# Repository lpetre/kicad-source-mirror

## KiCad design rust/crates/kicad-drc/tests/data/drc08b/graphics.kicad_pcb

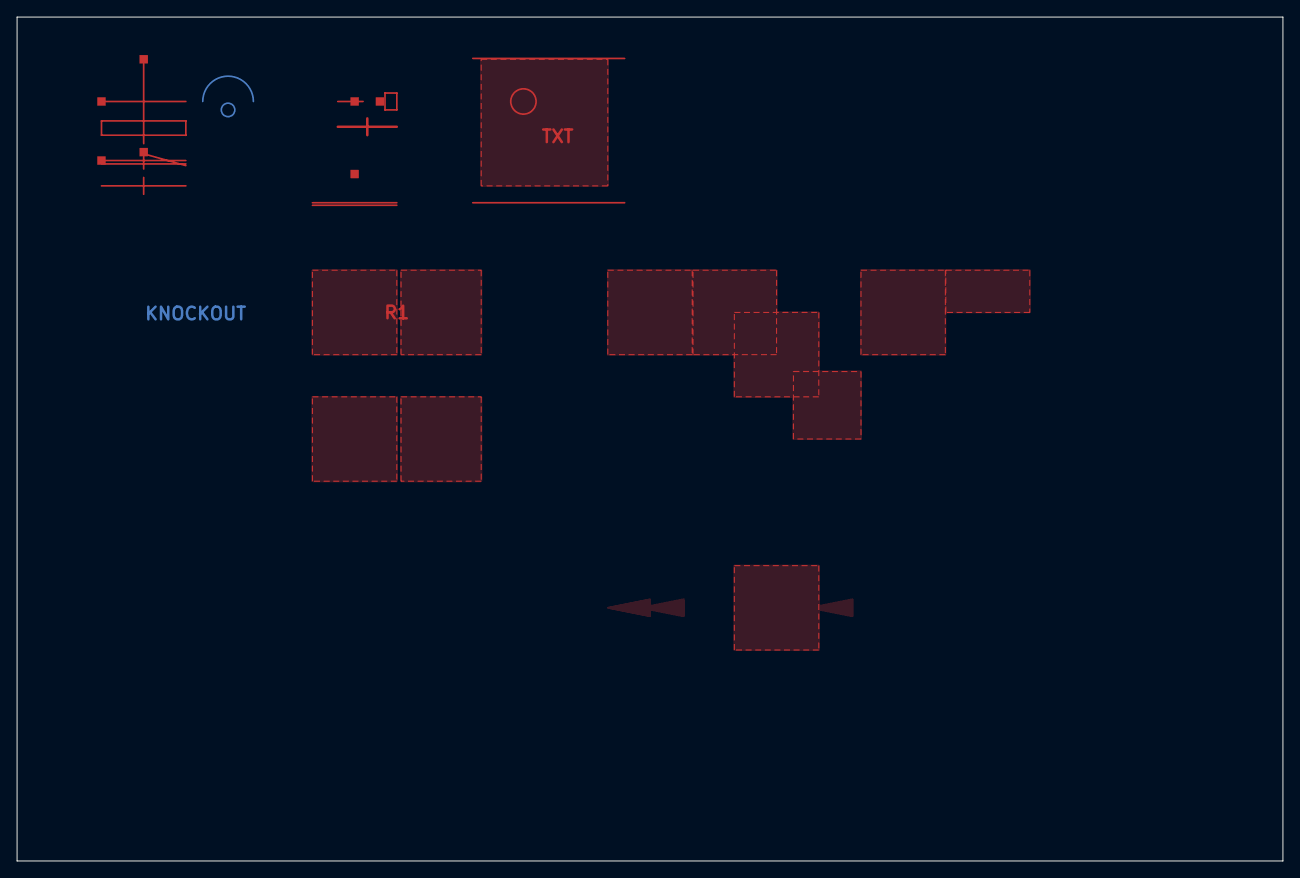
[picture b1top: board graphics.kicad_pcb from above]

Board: 4 copper layers, 150.0 x 100.0 mm, 5 parts (0 on the bottom side), 2 nets.

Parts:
R1: V; R1
R2: V; R2
U1: V; U1
U2: V; U2
U3: V; U3

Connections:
A: U1.1, U3.1, U3.3
B: U1.2, U3.2, U3.4
